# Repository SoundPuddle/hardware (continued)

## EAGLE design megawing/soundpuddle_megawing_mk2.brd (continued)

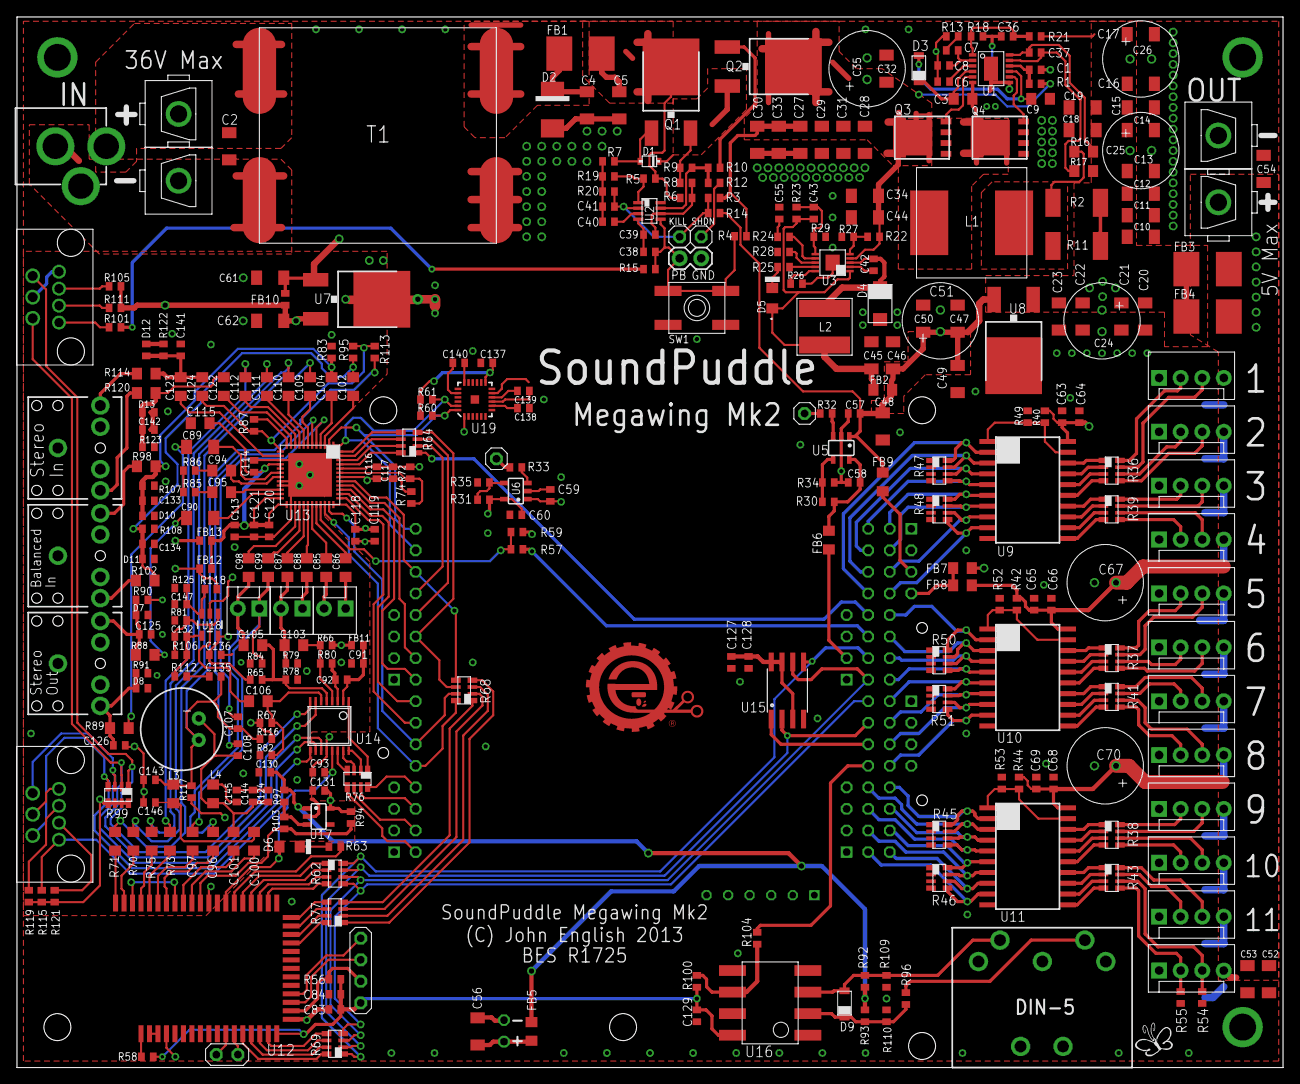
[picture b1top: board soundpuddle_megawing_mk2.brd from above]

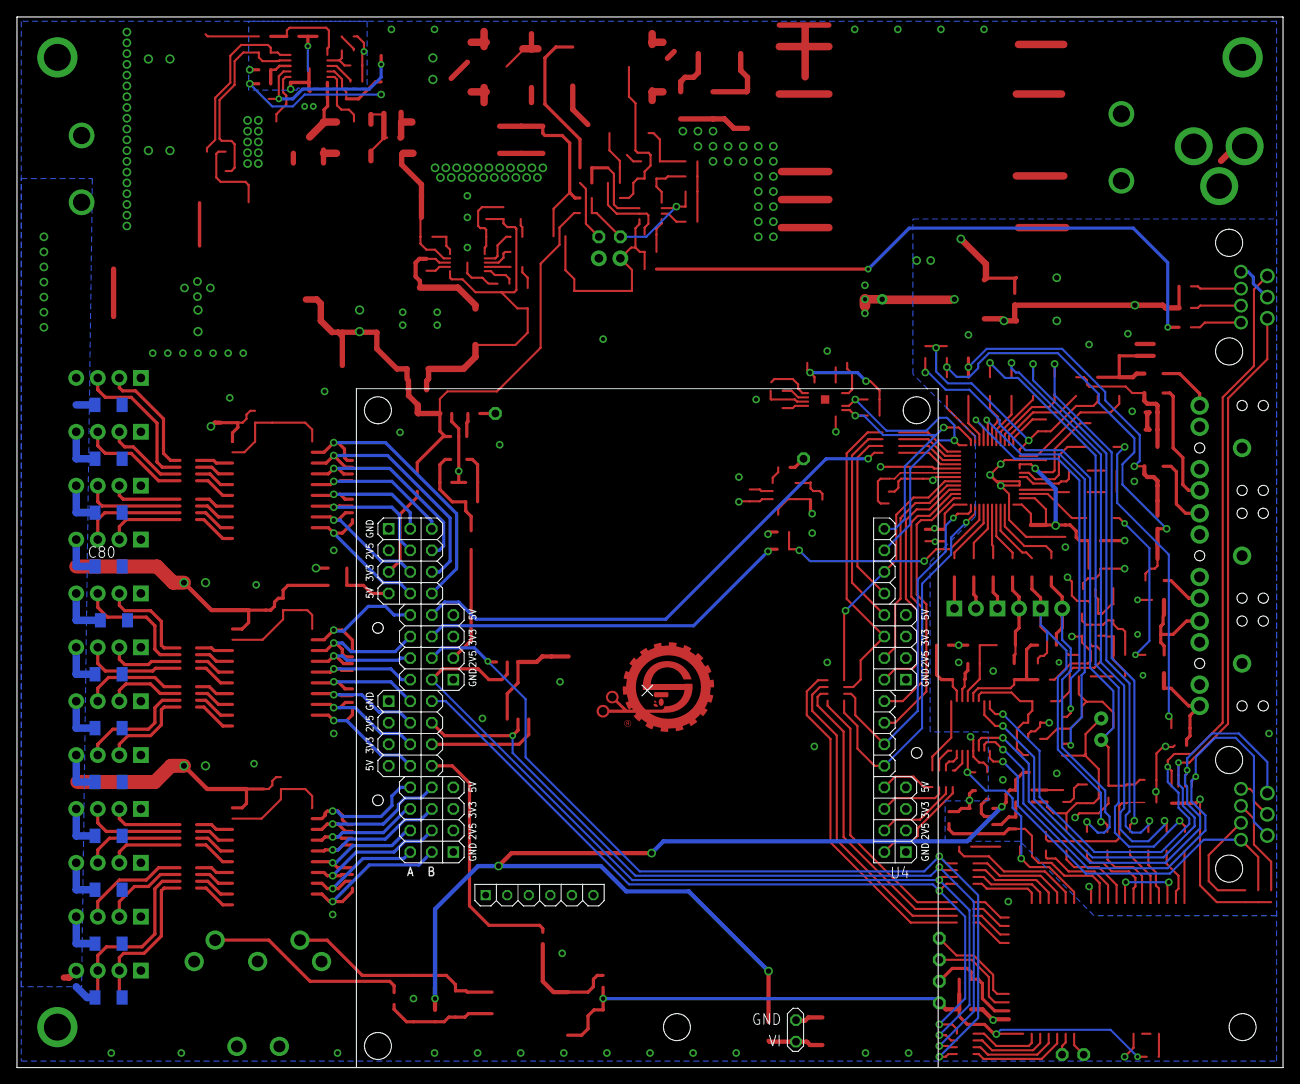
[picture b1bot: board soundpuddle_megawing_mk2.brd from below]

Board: 4 copper layers, 149.2 x 123.8 mm, 363 parts (13 on the bottom side), 279 nets.

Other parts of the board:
U$6: GADGETFACTORY_LOGO

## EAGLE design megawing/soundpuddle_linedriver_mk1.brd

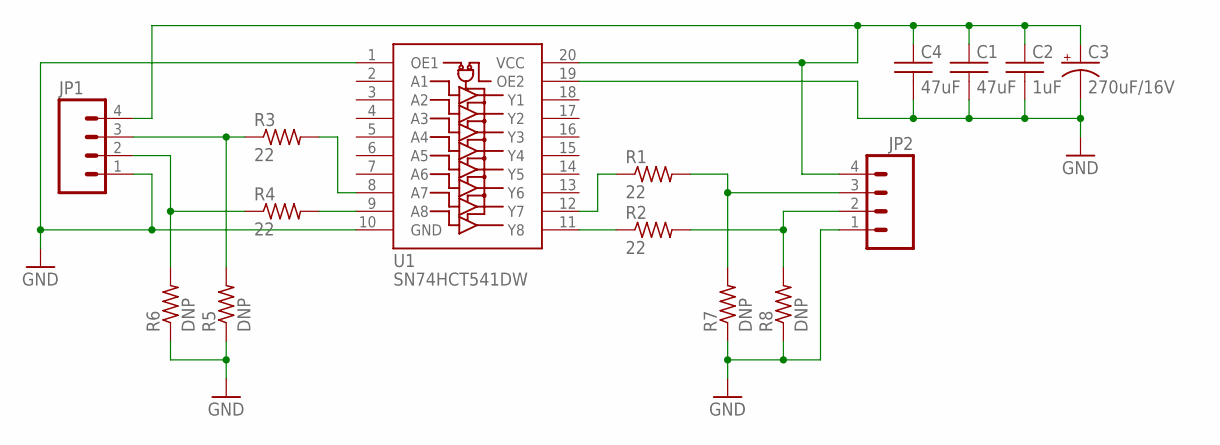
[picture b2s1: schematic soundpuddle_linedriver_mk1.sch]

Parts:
C1, C4: 47uF; 1206
C2: 1uF; 0603
C3: 270uF/16V; CAP_RADIAL_THRUHOLE_8MM_DIA
JP1, JP2: M04POLAR; MOLEX-1X4
R1, R2, R3, R4: 22; 0805
R5, R6, R7, R8: DNP; 0805
U1: SN74HCT541DW; SOIC-20_TI_DW

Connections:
GND: C1.P$2 (2), C2.2, C3.P$1 (-), C4.P$2 (2), JP1.1, JP2.1, R5.1, R6.1, R7.1, R8.1, U1.1 (OE1), U1.10 (GND), U1.19 (OE2)
unnamed: C1.P$1 (1), C2.1, C3.P$2 (+), C4.P$1 (1), JP1.4, JP2.4, U1.20 (VCC)
unnamed: JP1.2, R4.1, R6.2
unnamed: JP1.3, R3.1, R5.2
unnamed: R1.1, U1.12 (Y7)
unnamed: JP2.2, R2.2, R8.2
unnamed: JP2.3, R1.2, R7.2
unnamed: R2.1, U1.11 (Y8)
unnamed: R3.2, U1.8 (A7)
unnamed: R4.2, U1.9 (A8)

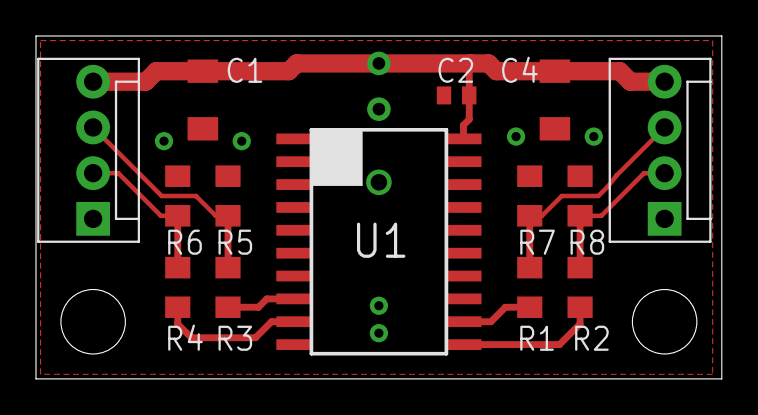
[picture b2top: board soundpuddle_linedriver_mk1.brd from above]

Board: 2 copper layers, 38.1 x 19.1 mm, 15 parts (1 on the bottom side), 10 nets.

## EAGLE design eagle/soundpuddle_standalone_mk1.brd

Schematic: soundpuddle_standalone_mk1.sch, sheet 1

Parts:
$2: changeme; 0603
$3: 3.6uH; INDUCTOR_HC1
C1, C3, C57, C84, C122, C124, C131, C139, C140, C141, C142, C143, C164, C169, C171, C184: 0.1uF; 0603
C2, C4, C14, C15, C18, C21, C26, C31, C43, C44, C53, C54, C58, C61, C104, C106, C107, C108, C109, C113, C127, C134, C136, C138: 1uF; 0603
C5, C6, C8, C9, C10: 10uF; 0805
C7, C17, C23, C25, C34, C45, C46, C47, C48, C56, C69, C70, C71, C72, C73, C74, C75, C76, C79, C80, C112, C115, C118: 1uF; 0805
C11: 22uF; 0603
C12, C13, C20, C130, C133: 22uF; 1206
C16, C126: 0.47uF; 0603
C19, C181, C185, C189, C190: CAPACITOR_ELEC6.3MM_DIA; CAP_RADIAL_THRUHOLE_6.3MM_DIA
C22, C24, C27, C28, C29, C35, C36, C40: 15pF; 0603
C30, C52: 10uF; 0603
C32, C33, C37, C41, C55, C60, C68, C105, C111, C114, C123, C148, C149, C151, C152, C153, C154, C155, C156, C157, C158, C159, C160, C161, C162, C163, C174, C176, C196, C197, C198: 47uF; 1206
C38, C39: 22nF; 0603
C42, C59, C77, C116: 10uF; 1206
C49, C63, C103: 1uF; 1206
C50, C51, C64, C65: 0.22uF; 0603
C62: 220pF; 0603
C66, C82, C110, C119: 33pF; 0603
C67, C117: DNP; 0603
C78, C81, C83, C101: 0.47uF; 0805
C85, C86, C87, C88, C89, C90, C91, C92, C93, C94, C95, C96, C97, C98, C99, C100: .1uF; 0603
C102, C125: 2.2uF; 0603
C120, C121, C165, C168: 22pF; 0603
C128: DNP; 1206
C129: 10pF; 0603
C132: 2.2mF; CAP_RADIAL_THRUHOLE_6.3MM_DIA
C135: 0.1uF; 1206
C137: 1nF; 0603
C144, C145, C146, C147: 1mF; E5-8,5
C150, C172, C173, C175: 47uF; 2220
C166, C183: 2200pF; 0603
C167, C170: 4.7uF; 0603
C177, C178, C191, C192, C193, C194, C195, C199: 100uF; 2220
C179, C180, C186, C187, C188: CAPACITOR_ELEC12.5MM; CAP_RADIAL_THRUHOLE_12.5MM_DIA
C182, C201: 100pF; 0603
C200: 4.7nF; 0603
D1: DNP; DIODE_DO-214AC
D2, D5, D6, D7, D14, D15: LED0603; LED_0603
D3, D13: DIODE_SMDDO-214AC; DIODE_DO-214AC
D4, D16: DIODE_SMDSOD-123F; SOD-123F
D8: DIODE_SMD603; 0603_D
D9: LED0805; LED_0805
D10, D11: RED; LED_0603
D12: DIODE_SMDSOD-323; SOD-323
D17: DIODE_SMDDO-214AB; DIODE_DO-214AB
IC1: LDODPAK; DPACK_1
IC2: MT48LC64M4A2; TSOP54-400
J1: POWER_JACKPTH; POWER_JACK_PTH
J2: AVR_SPI_PRG_6PTH; 2X3
JP1, JP2: M02JST-PTH-2; JST-2-PTH
JP3, JP26, JP28: AUDIO-JACK2PTH; AUDIO-JACK
JP4, JP7, JP11, JP12, JP14, JP18, JP21, JP24, JP27, JP29, JP33, JP34: M04POLAR; MOLEX-1X4
JP5, JP6, JP25, JP35: HEADER-SMALL-1PIN; HEADER-SMALL-1PIN-0.036IN
JP8, JP20, JP22, JP23, JP32: M02PTH; 1X02
JP9: M04PTH; 1X04
JP10, JP31, JP41: HEADER-SMALL-2PIN; HEADER-SMALL-2PIN-0.036IN
JP13, JP17: M02POLAR; MOLEX-1X2
JP15: HEADER-SMALL-3PIN; HEADER-SMALL-3PIN-0.036IN
JP16, JP19, JP36: M05PTH; 1X05
JP30, JP40: USBTHM; USB-MINIB-THM
JP37: HEADER-SMALL-4PIN; HEADER-SMALL-4PIN-0.036IN
JP38: MIDI_CONN_FEMALE_SUPPORT; DIN_5_FEMALE_SUPPORT
JP39: M06SIP; 1X06
L1, L2: INDUCTOR0603; 0603
L3: 6.8uH; INDUCTOR_10X10MM
L4, L5: 15nH; 0805
L6, L7, L8, L9: INDUCTOR0805; 0805
L10, L11, L12, L13: 15uH; 1206
L14: INDUCTOR10X10MM; INDUCTOR_10X10MM
LED1, LED2, LED3: LED0603; LED_0603
MIC1, MIC2: MIC9.7MM; MIC-9.7MM
OSC: 32Mhz; OSC1
Q1: MOSFET-P_CH_DUAL_ARRAYSOIC8; SOIC8
Q2, Q3, Q4, Q5: MOSFET-P_CHANNELDPACK; DPACK_1
Q6, Q7: MOSFET_N_CHANNELLFPAK; POWERPAK_SO-8_LFPAK
R1, R2, R13, R14, R22, R23, R33, R41, R56, R62, R65, R71, R101, R108, R135, R141, R148, R150, R158, R170, R171, R173, R176, R177, R188: DNP; 0603
R3, R8, R15, R28, R32, R63, R75, R82, R98, R100, R117, R119, R145, R151: RESISTOR_ARRAY_4CHCRA06S; RESISTOR_ARRAY_1206_4CH_CRA06S
R4, R5, R6, R7, R9, R10: 10; 0805
R11, R27, R30, R36, R49, R51, R52, R123, R127, R132, R162, R187, R191, R204: 1K; 0603
R12, R34, R37, R38, R39, R40, R53, R58, R59, R60, R66, R74, R104, R114, R116, R137, R143, R146, R159: 100K; 0603
R16, R180, R184, R185, R186, R194, R195: 7.5K; 0603
R17, R44, R61, R64, R80, R85, R91, R118, R120, R139, R142: 2.2K; 0603
R18: 0.033; 1206
R19, R57, R156: 1M; 0603
R20, R21, R24, R26, R45, R67, R76, R78, R79, R93, R94, R106, R131, R133, R144, R149, R157, R161, R165, R167, R168, R169, R172, R193: 10K; 0603
R25, R86, R88: 0; 0603
R29, R35, R77: 121K; 0603
R31: 1K; RESISTOR_ARRAY_1206_4CH_CRA06S
R42, R43, R72, R73, R121, R122: DNP; RESISTOR_ARRAY_1206_4CH_CRA06S
R46, R47, R48, R54, R55: changeme; 0603
R50, R196, R199: 47K; 0603
R68, R99, R147: TRIMPOT3MM-2; TRIMPOT-3MM-2
R69, R89, R92, R95, R96, R102, R107, R111, R113, R115, R125, R163: 1; 0805
R70, R84, R90, R128: 10K; 0805
R81, R83, R110, R124, R129, R140: 43K; 0603
R87: 22; RESISTOR_ARRAY_1206_4CH_CRA06S
R97, R103, R134, R136: 22K; 0603
R105, R138: 39; 0603
R109, R112: 22; 0805
R126, R130, R181, R182: 22; 0603
R152, R153, R164, R178: 330; 0603
R154, R155: 220; 0603
R160: 390; 0603
R166: 562K; 0603
R174, R175, R179: 68; 0603
R183: 1.5K; 0603
R189, R192: 0.006; 2512
R190: 2K; 0603
R197, R198: 16; 1206
R200: 8.06K; 0603
R201: 42.2K; 0603
RT1: 10K; 0603
S8: SWITCH-MOMENTARY-2PTH; TACTILE-PTH
SW3, SW5: SPST_TACT-KMR2; KMR2
U2: ADC128S102; TSSOP16
U3: LTC4002S8; S8_TI
U4, U24, U25: LDO_EN_FB; TSOT23
U5, U11, U14, U17: NJM2068M; DMP8_NJM
U6, U8, U16: SN74HCT541TSSOP20; TSSOP20
U7: LTC2952F; TSSOP20_LT
U9: TPA2008D2; TSSOP24+1_TI
U10: ADXL345; LGA14
U12: WT32; WT32_BT_MODULE
U13: USBLC6-2; SOT23-6L
U15: TPA6130A2QFN20; QFN20+1
U18, U20: TS5A22364DGS; MSOP10
U19: ATMEGA32U4AU; TQFP44
U21, U26: FLASH-SPI-25XXSMD1; SO08-EIAJ
U22: 6N138SMD8; SMD-8
U23: LT3971; MSOP10+1_LT
U27: 6SLX9TQG144; TQ144
U28: FT2232D; LQFP48
U29: 93C46B; SOT23-6
U30: LTC3891; TSSOP20+1_LT
X1: 16Mhz; ABRACOM_CLOCK
X2: ABRACOM_CLOCKS_ABABM10; ABRACOM_CLOCK
~NUDEV~: GND-GNDA

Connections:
1V2: C89.1, C90.1, C91.1, C92.1, U27.19 (VCCINT), U27.28 (VCCINT), U27.52 (VCCINT), U27.89 (VCCINT), U27.128 (VCCINT)
3V3: C85.1, C86.1, C87.1, C88.1, C93.1, C94.1, C95.1, C96.1, C97.1, C98.1, C99.1, C100.1, IC2.1 (VDD), IC2.3 (VDDQ), IC2.9 (VDDQ), IC2.14 (VDD), IC2.27 (VDD), IC2.43 (VDDQ), IC2.49 (VDDQ), OSC.1@1 (OE), OSC.4@4 (VCC), R199.2, U26.3 (WP), U26.7 (HOLD), U26.8 (VCC), U27.4 (VCCO_3), U27.18 (VCCO_3), U27.20 (VCCAUX), U27.31 (VCCO_3), U27.36 (VCCAUX), U27.42 (VCCO_2), U27.53 (VCCAUX), U27.63 (VCCO_2), U27.69 (IO_L1N_M0_CMPMISO_2), U27.76 (VCCO_1), U27.86 (VCCO_1), U27.90 (VCCAUX), U27.103 (VCCO_1), U27.122 (VCCO_0), U27.125 (VCCO_0), U27.129 (VCCAUX), U27.135 (VCCO_0)
3V3OUT_A: C142.2, U28.6 (3V3OUT)
!CAS: IC2.17 (!CAS), U27.5 (IO_L52N_3)
!RAS: IC2.18 (!RAS), U27.2 (IO_L83P_3)
!WE: IC2.16 (!WE), U27.6 (IO_L52P_3)
+3V3: C54.1, C57.1, C58.1, C59.P$1 (1), C106.1, C107.1, C108.1, C127.1, C128.P$1 (1), C129.1, C132.P$2 (+), C133.P$1 (1), C134.1, C135.P$1 (1), C138.1, D9.1 (A), D14.1 (A), J2.2, JP16.5, JP39.6, L2.1, L14.P$2 (2), LED1.1 (A), LED2.1 (A), R74.2, R75.P$4 (1), R131.2, R155.2, R156.2, R171.2, U10.1 (VDD), U10.6 (VSS), U10.7 (CS), U12.17 (VDDIO), U12.37 (VDD_BAT), U19.14 (VCC), U19.24 (AVCC), U19.34 (VCC), U19.44 (AVCC), U21.3 (WP), U21.7 (HOLD), U21.8 (VCC), U22.P$8 (VCC), U23.P$1 (BD), U24.1 (IN), U25.5 (OUT), U28.10 (SI/WUA), U28.14 (VCCIOA), U28.26 (SI/WUB), U28.31 (VCCIOB)
+5V: C18.1, C30.1, C31.1, C32.P$2 (2), C33.P$2 (2), C37.P$2 (2), C41.P$2 (2), C42.P$1 (1), C43.1, C44.1, C52.1, C53.1, C55.P$2 (2), C60.P$2 (2), C68.P$2 (2), C103.P$1 (1), C104.1, C105.P$2 (2), C111.P$2 (2), C114.P$2 (2), C123.P$2 (2), C139.1, C140.1, C144.+, C145.+, C146.+, C147.+, C148.P$1 (1), C149.P$1 (1), C150.P$1 (1), C151.P$1 (1), C152.P$1 (1), C153.P$1 (1), C154.P$1 (1), C155.P$1 (1), C156.P$1 (1), C157.P$1 (1), C158.P$1 (1), C159.P$1 (1), C160.P$1 (1), C161.P$1 (1), C162.P$1 (1), C163.P$1 (1), C164.1, C169.1, C185.P$2 (+), C186.P$2 (+), C187.P$2 (+), C188.P$2 (+), C189.P$2 (+), C190.P$2 (+), C191.P$1 (1), C192.P$1 (1), C193.P$1 (1), C194.P$1 (1), C195.P$1 (1), C196.P$1 (1), C197.P$1 (1), C198.P$1 (1), C199.P$1 (1), IC1.3 (2_VIN), JP4.4, JP7.4, JP11.4, JP12.4, JP14.4, JP18.4, JP21.4, JP24.4, JP27.4, JP29.4, JP33.4, JP34.4, R23.2, R31.P$6 (2), R31.P$7 (2), R31.P$8 (2), R33.2, R62.1, R65.1, R135.2, R152.2, R153.2, R180.1, R189.1, R191.2, R192.1, R193.1, R198.P$1 (1), R200.2, U4.1 (IN), U6.20 (VCC), U8.20 (VCC), U9.4 (PVDDL), U9.9 (PVDDL), U9.13 (VDD), U9.16 (PVDDR), U9.21 (PVDDR), U16.20 (VCC), U25.1 (IN), U28.3 (VCC), U28.4 (RESET#), U28.42 (VCC), U29.6 (VCC)
A0: IC2.23 (A0), U27.140 (IO_L3P_0)
A1: IC2.24 (A1), U27.139 (IO_L3N_0)
A2: IC2.25 (A2), U27.138 (IO_L4P_0)
A3: IC2.26 (A3), U27.137 (IO_L4N_0)
A4: IC2.29 (A4), U27.46 (IO_L49P_D3_2)
A5: IC2.30 (A5), U27.45 (IO_L49N_D4_2)
A6: IC2.31 (A6), U27.44 (IO_L62P_D5_2)
A7: IC2.32 (A7), U27.43 (IO_L62N_D6_2)
A8: IC2.33 (A8), U27.41 (IO_L64P_D8_2)
A9: IC2.34 (A9), U27.40 (IO_L64N_D9_2)
A10: IC2.22 (A10), U27.141 (IO_L2N_0)
A11: IC2.35 (A11), U27.35 (IO_L1P_3)
A12: IC2.36 (A12), U27.34 (IO_L1N_VREF_3)
ACC_INT1: JP15.P$1, U10.8 (INT1)
ACC_INT2: JP15.P$2, U10.9 (INT2)
ADC_CS: R8.P$8 (2)
ADC_IN2: C5.2, R1.1, R13.2
ADC_IN3: C6.2, R2.1, R14.2
ADC_IN4: C7.2, R3.P$1 (1), R15.P$8 (2), U2.7 (IN3)
ADC_IN5: C8.2, R3.P$2 (1), R15.P$7 (2), U2.6 (IN2)
ADC_IN6: C9.2, R3.P$3 (1), R15.P$6 (2), U2.5 (IN1)
ADC_IN7: C10.2, R3.P$4 (1), R15.P$5 (2), U2.4 (IN0)
ADC_MISO: R8.P$6 (2)
ADC_MOSI: R8.P$7 (2)
ADC_SCK: R8.P$5 (2)
AOL_N: R89.2, U18.4 (NC1)
AOL_P: R92.2, U18.8 (NC2)
AOR_N: R95.2, U20.4 (NC1)
AOR_P: R96.2, U20.8 (NC2)
AREF: C124.1, R135.1, R141.2, U19.42 (AREF)
ATMEGA_MISO: U19.11 (PB3(MISO))
ATMEGA_MOSI: U19.10 (PB2(MOSI))
ATMEGA_SCK: U19.9 (PB1(SCK))
AUX_IN_L: C56.1, JP26.TIP, R9.1
AUX_IN_L_N: R115.2, U18.2 (N01)
AUX_IN_L_P: R69.2, U18.10 (N02)
AUX_IN_R: C112.1, JP26.RING, R10.1
AUX_IN_R_N: R163.2, U20.2 (N01)
AUX_IN_R_P: R125.2, U20.10 (N02)
AUX_OUT_L: C116.P$2 (2), JP28.TIP, R6.1, R109.2, R137.2, R138.2
AUX_OUT_R: C77.P$2 (2), JP28.RING, R7.1, R104.2, R105.2, R112.2
BA0: IC2.20 (BA0), U27.143 (IO_L1N_VREF_0)
BA1: IC2.21 (BA1), U27.142 (IO_L2P_0)
BT_CLK: JP19.4, U12.33 (SPI_CLK)
BT_CTS: JP16.1, R75.P$8 (2)
BT_MIC_BIAS: R20.2, U12.40 (MIC_BIAS)
BT_MISO: JP19.3, U12.34 (SPI_MISO)
BT_MOSI: JP19.2, U12.35 (SPI_MOSI)
BT_PIO2: R98.P$4 (1)
BT_PIO3: R98.P$3 (1)
BT_PIO9: R87.P$1 (1)
BT_PIO10: R87.P$2 (1)
BT_RTS: JP16.2, R75.P$7 (2)
BT_RXD: R87.P$3 (1)
BT_SPICS: JP19.5, U12.32 (SPI_CS)
BT_TXD: R87.P$4 (1)
BUFFER_EN: R33.1, R44.2, U6.1 (OE1), U6.19 (OE2), U8.1 (OE1), U8.19 (OE2), U16.1 (OE1), U16.19 (OE2)
C4: R160.2
CKE: IC2.37 (CKE), U27.33 (IO_L2P_3)
CLK: IC2.38 (CLK), U27.32 (IO_L2N_3)
CS: IC2.19 (\CS), U27.1 (IO_L83N_VREF_3)
D+: JP30.D+, R130.2, R177.2, U13.1 (IO1A)
D+1: JP40.D+, R177.1, R182.1
D+_IC: R126.1, U19.3 (D-)
D-: JP30.D-, R126.2, R176.2, U13.3 (IO2A)
D-1: JP40.D-, R176.1, R181.1
D-_IC: R130.1, U19.4 (D+)
DO_A: R190.1, R193.2, U29.1 (DO)
DQ0: IC2.2 (DQ0), U27.9 (IO_L50N_3)
DQ1: IC2.4 (DQ1), U27.10 (IO_L50P_3)
DQ2: IC2.5 (DQ2), U27.11 (IO_L49N_3)
DQ3: IC2.7 (DQ3), U27.12 (IO_L49P_3)
DQ4: IC2.8 (DQ4), U27.14 (IO_L44N_GCLK20_3)
DQ5: IC2.10 (DQ5), U27.15 (IO_L44P_GCLK21_3)
DQ6: IC2.11 (DQ6), U27.16 (IO_L43N_GCLK22_IRDY2_3)
DQ7: IC2.13 (DQ7), U27.8 (IO_L51P_3)
DQ8: IC2.42 (DQ8), U27.21 (IO_L42N_GCLK24_3)
DQ9: IC2.44 (DQ9), U27.22 (IO_L42P_GCLK25_TRDY2_3)
DQ10: IC2.45 (DQ10), U27.23 (IO_L41N_GCLK26_3)
DQ11: IC2.47 (DQ11), U27.24 (IO_L41P_GCLK27_3)
DQ12: IC2.48 (DQ12), U27.26 (IO_L37N_3)
DQ13: IC2.50 (DQ13), U27.27 (IO_L37P_3)
DQ14: IC2.51 (DQ14), U27.29 (IO_L36N_3)
DQ15: IC2.53 (DQ15), U27.30 (IO_L36P_3)
DQMH: IC2.39 (DQMH), U27.17 (IO_L43P_GCLK23_3)
DQML: IC2.15 (DQML), U27.7 (IO_L51N_3)
EECS_A: U28.48 (EECS), U29.5 (CS)
EEDATA_A: R190.2, U28.2 (EEDATA), U29.3 (DI)
EESK: U28.1 (EESK), U29.4 (CLK)
EN: R45.1, U7.P$14 (EN)
FILTERED_VCC_A: C141.2, R191.1, U28.46 (AVCC)
FLASH_CS: U21.1 (CS), U26.1 (CS), U27.38 (IO_L65N_CSO_B_2)
FLASH_MISO: U21.2 (MISO)
FLASH_MOSI: U21.5 (MOSI)
FLASH_SCK: U21.6 (SCK), U26.6 (SCK), U27.70 (IO_L1P_CCLK_2)
FLASH_SI: U26.5 (MOSI), U27.64 (IO_L3N_MOSI_CSI_B_MISO0_2)
FLASH_SO: U26.2 (MISO), U27.65 (IO_L3P_D0_DIN_MISO_MISO1_2)
GND: $2.1, C1.2, C2.2, C3.2, C4.2, C11.2, C12.P$2 (2), C13.P$2 (2), C14.2, C15.2, C19.P$1 (-), C20.P$2 (2), C21.2, C30.2, C31.2, C32.P$1 (1), C33.P$1 (1), C37.P$1 (1), C38.2, C39.2, C41.P$1 (1), C52.2, C53.2, C54.2, C55.P$1 (1), C57.2, C58.2, C59.P$2 (2), C60.P$1 (1), C68.P$1 (1), C85.2, C86.2, C87.2, C88.2, C89.2, C90.2, C91.2, C92.2, C93.2, C94.2, C95.2, C96.2, C97.2, C98.2, C99.2, C100.2, C103.P$2 (2), C104.2, C105.P$1 (1), C106.2, C107.2, C108.2, C109.2, C111.P$1 (1), C113.2, C114.P$1 (1), C120.2, C121.2, C123.P$1 (1), C124.2, C127.2, C128.P$2 (2), C130.P$2 (2), C131.2, C132.P$1 (-), C133.P$2 (2), C134.2, C135.P$2 (2), C136.2, C137.2, C138.2, C139.2, C140.2, C141.1, C142.1, C143.2, C144.-, C145.-, C146.-, C147.-, C148.P$2 (2), C149.P$2 (2), C150.P$2 (2), C151.P$2 (2), C152.P$2 (2), C153.P$2 (2), C154.P$2 (2), C155.P$2 (2), C156.P$2 (2), C157.P$2 (2), C158.P$2 (2), C159.P$2 (2), C160.P$2 (2), C161.P$2 (2), C162.P$2 (2), C163.P$2 (2), C164.2, C165.1, C166.2, C167.2, C168.1, C169.2, C172.P$2 (2), C173.P$2 (2), C174.P$2 (2), C175.P$2 (2), C176.P$2 (2), C177.P$2 (2), C178.P$2 (2), C179.P$1 (-), C180.P$1 (-), C181.P$1 (-), C185.P$1 (-), C186.P$1 (-), C187.P$1 (-), C188.P$1 (-), C189.P$1 (-), C190.P$1 (-), C191.P$2 (2), C192.P$2 (2), C193.P$2 (2), C194.P$2 (2), C195.P$2 (2), C196.P$2 (2), C197.P$2 (2), C198.P$2 (2), C199.P$2 (2), D3.P$2 (A), D13.P$2 (A), D17.A, IC1.1 (1_GND), IC2.6 (VSSQ), IC2.12 (VSSQ), IC2.28 (VSS), IC2.41 (VSS), IC2.46 (VSSQ), IC2.52 (VSSQ), IC2.54 (VSS), J1.GND, J1.GNDBREAK, J2.6, JP1.1, JP2.1, JP4.1, JP7.1, JP9.1, JP11.1, JP12.1, JP14.1, JP15.P$3, JP18.1, JP19.1, JP21.1, JP24.1, JP27.1, JP29.1, JP30.GND, JP33.1, JP34.1, JP36.1, JP37.P$4, JP39.5, JP40.GND, JP41.P$1, LED3.2 (C), OSC.2@2 (GND), Q7.1S (S), Q7.2S (S), Q7.3S (S), R13.1, R14.1, R15.P$1 (1), R15.P$2 (1), R15.P$3 (1), R15.P$4 (1), R17.2, R35.1, R42.P$1 (1), R42.P$2 (1), R42.P$3 (1), R42.P$4 (1), R43.P$1 (1), R43.P$2 (1), R43.P$3 (1), R43.P$4 (1), R44.1, R54.1, R55.1, R72.P$1 (1), R72.P$2 (1), R72.P$3 (1), R72.P$4 (1), R73.P$1 (1), R73.P$2 (1), R73.P$3 (1), R73.P$4 (1), R90.2, R121.P$1 (1), R121.P$2 (1), R121.P$3 (1), R121.P$4 (1), R122.P$1 (1), R122.P$2 (1), R122.P$3 (1), R122.P$4 (1), R123.2, R127.2, R132.2, R141.1, R164.1, R165.1, R166.1, R168.1, R169.1, R170.1, R173.1, R178.1, RT1.2, S8.1, SW3.2 (S), SW3.4 (S1), SW5.2 (S), SW5.4 (S1), U2.3 (AGND), U2.12 (DGND), U3.P$4 (GND), U6.10 (GND), U7.P$12 (GND), U8.10 (GND), U9.6 (PGNDL), U9.7 (PGNDL), U9.18 (PGNDR), U9.19 (PGNDR), U10.2 (GND), U10.4 (GND), U10.5 (GND), U10.12 (SDO), U12.2 (DGND), U12.3 (DGND), U12.4 (DGND), U12.18 (DGND), U12.31 (DGND), U13.2 (GND), U16.10 (GND), U19.5 (UGND), U19.15 (GND), U19.23 (GND), U19.35 (GND), U19.43 (GND), U21.4 (GND), U22.P$5 (GND), U23.P$11 (GND), U24.2 (GND), U25.2 (GND), U26.4 (GND), U27.3 (GND), U27.13 (GND), U27.25 (GND), U27.49 (GND), U27.54 (GND), U27.60 (IO_L13P_M1_2), U27.68 (GND), U27.73 (SUSPEND), U27.77 (GND), U27.91 (GND), U27.96 (GND), U27.108 (GND), U27.113 (GND), U27.130 (GND), U27.136 (GND), U27.144 (IO_L1P_HSWAPEN_0), U28.9 (GND), U28.18 (GND), U28.25 (GND), U28.34 (GND), U28.45 (GND), U28.47 (TEST), U29.2 (GND), U30.P$11 (PGND), X1.2, X1.4, X2.2, X2.4
GNDA: C17.2, C18.2, C24.1, C26.2, C27.2, C28.2, C29.2, C40.2, C42.P$2 (2), C43.2, C44.2, C50.2, C51.2, C61.2, C62.2, C64.2, C65.2, C73.2, C74.2, C75.2, C84.2, C102.2, C122.2, C125.2, JP3.SLEEVE, JP8.1, JP20.1, JP26.SLEEVE, JP28.SLEEVE, JP31.P$1, MIC2.1, R26.1, R27.1, R58.1, R59.1, R68.3 (CW), R71.1, R76.1, R77.1, R104.1, R106.1, R116.1, R137.1, R146.1, R149.1, U4.2 (GND), U5.4 (V-), U9.12 (AGND), U9.PGND (AGND), U11.4 (V-), U12.39 (AGND), U12.43 (AGND), U12.48 (AGND), U14.4 (V-), U15.P$3 (GND), U15.P$9 (GND), U15.P$10 (GND), U15.P$13 (GND), U15.P$19 (GND), U15.PAD (GND), U17.4 (V-), U18.6 (GND), U20.6 (GND)
GNDIO: C171.2, C182.2, C183.2, C184.2, C201.2, R188.1, R195.1, R201.1, U30.P$4 (SGND), U30.P$5 (SGND), U30.PAD (SGND)
LED1: R196.2, U27.112 (IO_L66P_SCP1_0)
LED_B1: U19.30 (PB6(D10*/A11))
LED_G1: U19.31 (PC6(D5*))
LED_R1: U19.32 (PC7(D13*))
LOUT_N: C45.1, C78.1, C80.1, U18.3 (COM1)
LOUT_P: C46.1, C76.1, C81.1, U18.9 (COM2)
MIC_DYNAMIC: R4.1, R66.2, U5.7 (OUT)
MIC_ELECTRET: C22.2, R5.1, R19.2, U5.1 (OUT)
MIC_N: C25.1, C28.1, C69.2, L5.1
MIC_P: C23.1, C29.1, C70.2, L4.1
MIC_REG: C17.1, R30.2, R84.2, U4.5 (OUT)
MISO: J2.1
MOSI: J2.4
MUX_IN1: JP31.P$2, R145.P$5 (2), R145.P$6 (2), R145.P$7 (2), R145.P$8 (2), U19.12 (PB7(D11*))
unnamed: C120.1, U19.16 (XTAL2), X1.3 (3A)
unnamed: C35.1, R50.2, R52.2, U5.5 (+)
unnamed: C5.1, R4.2
unnamed: C36.1, R40.1, R50.1, R53.1, R59.2
unnamed: R94.2, U15.P$6 (SD)
unnamed: D11.2 (C), R132.1
unnamed: C112.2, R128.1
unnamed: R20.1, R23.1, U4.3 (EN)
unnamed: C56.2, R70.1
unnamed: R96.1, U12.47 (AUDIO_OUT_P_RIGHT)
unnamed: C121.1, U19.17 (XTAL1), X1.1 (1A)
unnamed: C26.1, R21.1, R25.2, R26.2, U5.3 (+)
unnamed: R123.1, U19.33 (PE2(HWB))
unnamed: L3.P$2 (2), R18.P$2 (2), U3.P$7 (SENSE)
unnamed: R183.2, U28.5 (RSTOUT#)
unnamed: R36.2, U7.P$19 (G1)
unnamed: C45.2, L6.1
unnamed: C113.1, U19.6 (UCAP)
unnamed: D2.1 (A), R11.1
unnamed: C46.2, L7.1
unnamed: C47.2, L8.1
unnamed: C48.2, L9.1
unnamed: R77.2, U9.11 (ROSC)
unnamed: C62.1, U9.10 (COSC)
unnamed: C7.1, R6.2
unnamed: C49.P$1 (1), C50.1, JP13.1, L10.P$2 (2)
unnamed: Q4.1 (G), Q5.1 (G), R36.1
unnamed: L10.P$1 (1), U9.8 (LOUTN)
unnamed: C61.1, U9.22 (BYPASS)
unnamed: L11.P$1 (1), U9.5 (LOUTP)
unnamed: C49.P$2 (2), C51.1, JP13.2, L11.P$2 (2)
unnamed: L13.P$1 (1), U9.20 (ROUTP)
unnamed: L12.P$1 (1), U9.17 (ROUTN)
unnamed: C63.P$1 (1), C64.1, JP17.2, L12.P$2 (2)
unnamed: C63.P$2 (2), C65.1, JP17.1, L13.P$2 (2)
unnamed: JP36.3, R151.P$6 (2)
unnamed: JP36.2, R151.P$5 (2)
unnamed: Q2.1 (G), Q3.1 (G), U7.P$15 (G2)
unnamed: R29.1, R35.2, R41.1, U7.P$5 (PFI)
unnamed: L9.2, U9.23 (RINP)
unnamed: L8.2, U9.24 (RINN)
unnamed: L7.2, U9.2 (LINP)
unnamed: L6.2, U9.1 (LINN)
unnamed: C27.1, JP3.RING, L5.2, MIC1.1, R27.2
unnamed: C24.2, JP3.TIP, L4.2, MIC1.2, R22.1, R30.1
unnamed: C69.1, U12.44 (AUDIO_IN_P_LEFT)
unnamed: C70.1, U12.45 (AUDIO_IN_N_LEFT)
unnamed: S8.3 (2), U7.P$7 (_PB)
unnamed: R48.1, R55.2, U7.P$1 (M2)
unnamed: $2.2, R47.1, U7.P$2 (M1)
unnamed: R80.1, U12.36 (LED0)
unnamed: Q1.4 (G), U3.P$3 (GATE)
unnamed: C13.P$1 (1), C14.1, C15.1, D1.P$1 (C), Q1.1 (S), Q1.3 (S), U3.P$2 (VCC)
unnamed: R98.P$5 (2), U12.9 (PIO2)
unnamed: C23.2, R24.1
unnamed: C16.1, U3.P$1 (COMP)
unnamed: C16.2, R17.1
unnamed: RT1.1, U3.P$8 (NTC)
unnamed: D3.P$1 (C), L3.P$1 (1), Q1.5 (D), Q1.6 (D)
unnamed: R98.P$6 (2), U12.10 (PIO3)
unnamed: R87.P$8 (2), U12.13 (PIO9)
unnamed: R87.P$7 (2), U12.14 (PIO10)
unnamed: R95.1, U12.46 (AUDIO_OUT_N_RIGHT)
unnamed: D9.2 (C), R80.2
unnamed: C67.2, R61.2, R78.2, R91.2, R108.2, R115.1, U11.7 (OUT)
unnamed: R92.1, U12.50 (AUDIO_OUT_P_LEFT)
unnamed: R98.P$1 (1), U13.4 (IO2B)
unnamed: JP16.4, R75.P$5 (2)
unnamed: C39.1, U7.P$11 (OFFT)
unnamed: JP16.3, R75.P$6 (2)
unnamed: R98.P$8 (2), U12.12 (USB_DP)
unnamed: R98.P$7 (2), U12.11 (USB_DN)
unnamed: C25.2, R25.1
unnamed: JP36.5, R151.P$8 (2)
unnamed: C38.1, U7.P$10 (ONT)
unnamed: D5.1 (A), R31.P$2 (1)
unnamed: D7.1 (A), R31.P$3 (1)
unnamed: Q2.3 (S), Q3.3 (S)
unnamed: D6.1 (A), R31.P$1 (1)
unnamed: D5.2 (C), U7.P$8 (_RST)
unnamed: LED3.1 (A), R196.1
unnamed: C126.2, D13.P$1 (C), L14.P$1 (1), U23.P$3 (SW)
unnamed: D6.2 (C), U7.P$20 (G1STAT)
unnamed: R87.P$6 (2), U12.15 (RXD)
unnamed: R87.P$5 (2), U12.16 (TXD)
unnamed: D7.2 (C), U7.P$9 (_PFO)
unnamed: C22.1, R19.1, R24.2, U5.2 (-)
unnamed: JP9.4, U7.P$13 (_INT)
unnamed: R49.2, U7.P$18 (V1)
unnamed: R51.2, U7.P$16 (V2)
unnamed: C126.1, U23.P$2 (BOOST)
unnamed: R98.P$2 (1), U13.6 (IO1B)
unnamed: C101.2, R113.1
unnamed: C83.2, R111.1
unnamed: C81.2, R107.1
unnamed: C78.2, R102.1
unnamed: R102.2, U15.P$1 (LEFTINM)
unnamed: R107.2, U15.P$2 (LEFTINP)
unnamed: R75.P$1 (1), U12.21 (CTS)
unnamed: R75.P$2 (1), U12.20 (RTS)
unnamed: R111.2, U15.P$5 (RIGHTINM)
unnamed: R113.2, U15.P$4 (RIGHTIMP)
unnamed: R74.1, R79.2, U12.1 (VREG_ENA)
unnamed: C35.2, C36.2
unnamed: C73.1, U15.P$15 (CPVSS), U15.P$16 (CPVSS)
unnamed: R109.1, U15.P$14 (HPLEFT)
unnamed: C79.1, U15.P$18 (CPP)
unnamed: C79.2, U15.P$17 (CPN)
unnamed: D8.ANNODE(1) (A), R79.1
unnamed: R112.1, U15.P$11 (HPRIGHT)
unnamed: C34.2, R52.1
unnamed: C6.1, R5.2
unnamed: R172.2, U25.3 (EN)
unnamed: C34.1, JP8.2, MIC2.2, R37.1, R38.1, R39.1, R58.2
unnamed: R57.1, U5.6 (-)
unnamed: R89.1, U12.49 (AUDIO_OUT_N_LEFT)
unnamed: C117.2, R118.2, R133.2, R142.2, R150.2, R163.1, U17.7 (OUT)
unnamed: R120.2, R125.1, R139.2, U17.1 (OUT)
unnamed: C40.1, R60.1
unnamed: R57.2, R60.2, R66.1
unnamed: JP6.P$1, R40.2
unnamed: R75.P$3 (1), U12.19 (RESET)
unnamed: LED1.2 (C), R187.2
unnamed: R171.1, R173.2, U25.4 (FB)
unnamed: D14.2 (C), R162.2
unnamed: Q4.3 (S), Q5.3 (S)
unnamed: R162.1, U23.P$9 (PG)
unnamed: D2.2 (C), Q1.2 (G), R12.1, U3.P$5 (CHRG)
unnamed: R100.P$8 (2), U12.27 (PCM_IN)
unnamed: R158.1, R170.2, U24.4 (FB)
unnamed: C129.2, R156.1, R166.2, U23.P$6 (FB)
unnamed: R100.P$7 (2), U12.28 (PCM_OUT)
unnamed: C66.1, JP22.2, R81.1, R97.2, R99.2 (WIPER), U14.2 (-)
unnamed: C82.1, R103.2, R110.2, U14.3 (+)
unnamed: C76.2, R97.1
unnamed: C80.2, R103.1
unnamed: C71.1, U12.41 (AUDIO_IN_P_RIGHT)
unnamed: C72.1, U12.42 (AUDIO_IN_N_RIGHT)
unnamed: C66.2, C77.P$1 (1), R81.2, R83.2, U14.1 (OUT)
unnamed: C82.2, C102.1, R110.1, R114.1, R116.2
unnamed: C84.1, R105.1
unnamed: R167.2, U24.3 (EN)
unnamed: R165.2, U23.P$10 (SYNC)
unnamed: JP32.2, R129.1, R147.2 (WIPER)
unnamed: C119.1, R136.2, R140.2, U14.5 (+)
unnamed: C115.2, R134.1
unnamed: C118.2, R136.1
unnamed: C137.1, R159.1
unnamed: R139.1, R142.1, U17.6 (-)
unnamed: C110.2, C116.P$1 (1), R124.2, R129.2, U14.7 (OUT)
unnamed: C119.2, C125.1, R140.1, R143.1, R146.2
unnamed: R169.2, U23.P$8 (RT)
unnamed: C122.1, R138.1
unnamed: JP5.P$1, R38.2
unnamed: R100.P$6 (2), U12.29 (PCM_SYNC)
unnamed: R159.2, U23.P$7 (SS)
unnamed: R145.P$4 (1), U18.5 (IN1)
unnamed: R145.P$3 (1), U18.7 (IN2)
unnamed: R100.P$5 (2), U12.30 (PCM_CLK)
unnamed: R157.1, R161.2, R168.2, U23.P$5 (EN)
unnamed: LED2.2 (C), R204.2
unnamed: JP37.P$2, JP38.5 (MIDI_OUT), R154.1
unnamed: JP36.4, R151.P$7 (2)
unnamed: R145.P$2 (1), U20.5 (IN1)
unnamed: R145.P$1 (1), U20.7 (IN2)
unnamed: D12.C, R153.1, R154.2, R164.2, U22.P$2 (A)
unnamed: R118.1, R120.1, U17.2 (-)
unnamed: R85.1, R91.1, U11.6 (-)
unnamed: C117.1, R128.2, R133.1, U17.3 (+)
unnamed: JP35.P$1, R148.1
unnamed: C8.1, R7.2
unnamed: R144.1, R148.2, R149.2, R150.1, U17.5 (+)
unnamed: D12.A, JP37.P$1, JP38.4 (MIDI_IN), R152.1, R178.2, U22.P$3 (C)
unnamed: JP22.1, R83.1, R99.3 (CW)
unnamed: R61.1, R64.1, U11.2 (-)
unnamed: C67.1, R70.2, R78.1, U11.3 (+)
unnamed: R155.1, R160.1, U22.P$6 (VO)
unnamed: C72.2, JP23.1, R90.1
unnamed: R93.1, R101.2, R106.2, R108.1, U11.5 (+)
unnamed: JP25.P$1, R101.1
unnamed: C71.2, JP23.2, R84.1
unnamed: C110.1, JP32.1, R124.1, R134.2, R147.3 (CW), U14.6 (-)
unnamed: R32.P$1 (1), U6.14 (Y5)
unnamed: R28.P$1 (1), U6.18 (Y1)
unnamed: R28.P$2 (1), U6.17 (Y2)
unnamed: R28.P$3 (1), U6.16 (Y3)
unnamed: R28.P$4 (1), U6.15 (Y4)
unnamed: R32.P$2 (1), U6.13 (Y6)
unnamed: R32.P$3 (1), U6.12 (Y7)
unnamed: R32.P$4 (1), U6.11 (Y8)
unnamed: JP11.2, R32.P$8 (2)
unnamed: JP11.3, R32.P$7 (2)
unnamed: JP7.3, R28.P$5 (2)
unnamed: JP7.2, R28.P$6 (2)
unnamed: JP4.3, R28.P$7 (2)
unnamed: JP4.2, R28.P$8 (2)
unnamed: C3.1, C4.1, L2.2, U2.13 (VD)
unnamed: C1.1, C2.1, L1.2, U2.2 (VA)
unnamed: D10.2 (C), R127.1
unnamed: R82.P$1 (1), U8.14 (Y5)
unnamed: R63.P$1 (1), U8.18 (Y1)
unnamed: R63.P$2 (1), U8.17 (Y2)
unnamed: R63.P$3 (1), U8.16 (Y3)
unnamed: R63.P$4 (1), U8.15 (Y4)
unnamed: R82.P$2 (1), U8.13 (Y6)
unnamed: R82.P$3 (1), U8.12 (Y7)
unnamed: R82.P$4 (1), U8.11 (Y8)
unnamed: JP21.2, R82.P$8 (2)
unnamed: JP21.3, R82.P$7 (2)
unnamed: JP18.3, R63.P$5 (2)
unnamed: JP18.2, R63.P$6 (2)
unnamed: JP14.3, R63.P$7 (2)
unnamed: JP14.2, R63.P$8 (2)
unnamed: R64.2, R69.1, R85.2, U11.1 (OUT)
unnamed: R119.P$1 (1), U16.14 (Y5)
unnamed: R117.P$1 (1), U16.18 (Y1)
unnamed: $3.P$1 (1), C170.2, D17.C, Q6.1S (S), Q6.2S (S), Q6.3S (S), Q7.PAD (D), Q7.PAD2 (D), U30.P$13 (SW)
unnamed: R117.P$2 (1), U16.17 (Y2)
unnamed: R117.P$3 (1), U16.16 (Y3)
unnamed: C182.1, R194.2, U30.P$10 (ITH)
unnamed: C200.1, R197.P$2 (2), U30.P$8 (SENSE+)
unnamed: C200.2, R198.P$2 (2), U30.P$7 (SENSE-)
unnamed: $3.P$2 (2), R189.2, R192.2, R197.P$1 (1)
unnamed: C167.1, D16.P$2 (A), R16.2, U30.P$16 (INTVCC)
unnamed: R117.P$4 (1), U16.15 (Y4)
unnamed: R119.P$2 (1), U16.13 (Y6)
unnamed: R119.P$3 (1), U16.12 (Y7)
unnamed: R119.P$4 (1), U16.11 (Y8)
unnamed: JP33.2, R119.P$8 (2)
unnamed: JP33.3, R119.P$7 (2)
unnamed: JP29.3, R117.P$5 (2)
unnamed: JP29.2, R117.P$6 (2)
unnamed: JP27.2, R117.P$8 (2)
unnamed: JP12.2, R32.P$6 (2)
unnamed: C184.1, U30.P$1 (TRACK/SS)
unnamed: R195.2, U30.P$2 (FREQ)
unnamed: C183.1, R194.1
unnamed: Q7.4G (G), U30.P$15 (BG)
unnamed: Q6.4G (G), U30.P$12 (TG)
unnamed: C170.1, D16.P$1 (C), U30.P$14 (BOOST)
unnamed: C201.1, R200.1, R201.2, U30.P$9 (VFB)
unnamed: R185.2, U30.P$6 (RUN)
unnamed: D15.2 (C), R184.1
unnamed: R16.1, R188.2, U30.P$3 (PLLIN/MODE)
unnamed: R186.2, U30.P$20 (ILIM)
unnamed: C166.1, R180.2, U30.P$17 (EXTVCC)
unnamed: JP12.3, R32.P$5 (2)
unnamed: JP24.2, R82.P$6 (2)
unnamed: JP24.3, R82.P$5 (2)
unnamed: JP34.2, R119.P$6 (2)
unnamed: JP34.3, R119.P$5 (2)
unnamed: JP27.3, R117.P$7 (2)
unnamed: R88.2, U15.P$8 (SCL)
unnamed: R86.2, U15.P$7 (SDA)
unnamed: R8.P$4 (1), U2.16 (SCLK)
unnamed: R8.P$2 (1), U2.14 (DIN)
unnamed: R8.P$1 (1), U2.1 (CS)
unnamed: R8.P$3 (1), U2.15 (DOUT)
unnamed: C10.1, R10.2
unnamed: C9.1, R9.2
unnamed: R204.1, U28.27 (BCBUS3)
unnamed: R187.1, U28.28 (BCBUS2)
OSC_IN: OSC.3@3 (OUT), U27.94 (IO_L40N_GCLK10_1)
PGOOD: R184.2, U30.P$18 (PGOOD)
PWR_DOWN: JP10.P$1, R34.2, R45.2, R56.2, R161.1, R167.1, R172.1, R185.1
REBOOT: JP41.P$2, R199.1, SW3.1, SW3.3 (P1), U27.37 (PROGRAM_B_2)
RESET: J2.5, R131.1, SW5.1, SW5.3 (P1), U19.13 (_RESET)
ROT1_A: R151.P$1 (1), U19.25 (PD4(D4/A6))
ROT1_B: R151.P$2 (1), U19.26 (PD6(D12/A7))
ROT2_A: R151.P$3 (1), U19.1 (PE6(D7)), U19.27 (PD7(D6*/A8))
ROT2_B: R151.P$4 (1), U19.28 (PB4(D8/A9))
ROUT_N: C47.1, C83.1, C118.1, U20.3 (COM1)
ROUT_P: C48.1, C101.1, C115.1, U20.9 (COM2)
RXD: U19.20 (PD2(INT2/RXD1/D0))
RXLED: D10.1 (A), U19.8 (PB0(SS){RXLED})
SCK: J2.3
SCL: R88.1, U19.18 (PD0(INT0/SCL/D3))
SCL_B: U10.14 (SCL)
SDA: R86.1, U19.19 (PD1(INT1/SDA/D2))
SDA_B: U10.13 (SDA)
SHUTDOWN: D8.CATHODE(2) (C), JP10.P$2, R56.1, R67.1, R94.1
TCK: JP39.4, R174.2, U27.109 (TCK)
TDI: JP39.2, R175.2, U27.110 (TDI)
TDO: JP39.3, U27.106 (TDO), U28.22 (ADBUS2)
TMS: JP39.1, R179.2, U27.107 (TMS)
TPA2008_EN: R65.2, R67.2, R76.2, U9.3 (_SHTDN)
TPA2008_VOL: JP20.2, R62.2, R68.2 (WIPER), R71.2, U9.14 (VOLUME)
TXD: U19.21 (PD3(INT3/TXD1/D1))
TXLED: D11.1 (A), U19.22 (PD5(TXLED))
USBDM_A: R181.2, U28.8 (USBDM)
USBDP_A: R182.2, R183.1, U28.7 (USBDP)
USB_ID: JP30.ID
USB_RXD: U27.105 (IO_L1P_1), U28.39 (BDBUS1)
USB_TCK: R174.1, U28.24 (ADBUS0)
USB_TDI: R175.1, U28.23 (ADBUS1)
USB_TMS: R179.1, U28.21 (ADBUS3)
USB_TXD: U27.101 (IO_L32N_1), U28.40 (BDBUS0)
VBATT: C19.P$2 (+), C20.P$1 (1), C21.1, JP1.2, Q4.2/HEAT (D), R18.P$1 (1), R46.2, R47.2, R49.1, U3.P$6 (BATT)
VBUS: C109.1, C143.1, D4.P$2 (A), JP30.VBUS, JP40.VBUS, U13.5 (VBUS), U19.2 (UVCC), U19.7 (VBUS)
VCCIO: C74.1, C75.1, IC1.2/HEAT (3_OUT), L1.1, R1.2, R2.2, R3.P$5 (2), R3.P$6 (2), R3.P$7 (2), R3.P$8 (2), R21.2, R22.2, R37.2, R53.2, R93.2, R114.2, R143.2, R144.2, U5.8 (V+), U11.8 (V+), U14.8 (V+), U15.P$12 (VDD), U15.P$20 (VDD), U17.8 (V+), U18.1 (VCC), U20.1 (VCC)
VDD: C136.1, R158.2, U24.5 (OUT)
VIN: C130.P$1 (1), C131.1, C172.P$1 (1), C173.P$1 (1), C174.P$1 (1), C175.P$1 (1), C176.P$1 (1), C177.P$1 (1), C178.P$1 (1), C179.P$2 (+), C180.P$2 (+), C181.P$2 (+), D15.1 (A), Q3.2/HEAT (D), Q5.2/HEAT (D), Q6.PAD (D), Q6.PAD2 (D), R29.2, R34.1, R39.2, R157.2, U7.P$17 (VS), U23.P$4 (VIN), U30.P$19 (VIN)
VM: R46.1, R54.2, U7.P$4 (VM)
VWALL: C11.1, C12.P$1 (1), D1.P$2 (A), D4.P$1 (C), J1.PWR, JP2.2, Q1.7 (D), Q1.8 (D), Q2.2/HEAT (D), R11.2, R12.2, R41.2, R48.2, R51.1
W1_A1: R122.P$6 (2), U16.8 (A7), U27.48 (IO_L48P_D7_2)
W1_A2: R122.P$8 (2), U16.6 (A5), U27.51 (IO_L31P_GCLK31_D14_2)
W1_A3: R121.P$6 (2), U16.4 (A3), U27.56 (IO_L30P_GCLK1_D13_2)
W1_A4: R121.P$8 (2), U16.2 (A1), U27.58 (IO_L14P_D11_2)
W1_A5: R43.P$6 (2), U6.8 (A7), U27.61 (IO_L12N_D2_MISO3_2)
W1_A6: R43.P$8 (2), U6.6 (A5), U27.66 (IO_L2N_CMPMOSI_2)
W1_A7: R42.P$5 (2), U6.5 (A4), U27.67 (IO_L2P_CMPCLK_2)
W1_A8: R42.P$7 (2), U6.3 (A2), U27.75 (IO_L74P_AWAKE_1)
W1_A9: R73.P$5 (2), U8.9 (A8), U27.79 (IO_L47P_1)
W1_A10: R73.P$6 (2), U8.8 (A7), U27.81 (IO_L46P_1)
W1_A11: R73.P$8 (2), U8.6 (A5), U27.83 (IO_L45P_1)
W1_A12: R72.P$6 (2), U8.4 (A3), U27.85 (IO_L43P_GCLK5_1)
W1_A13: R72.P$8 (2), U8.2 (A1), U27.88 (IO_L42P_GCLK7_1)
W1_A14: U27.93 (IO_L41P_GCLK9_IRDY1_1)
W1_A15: U27.98 (IO_L34P_1)
W1_A16: U27.100 (IO_L33P_1)
W1_B1: U27.99 (IO_L33N_1)
W1_B2: U27.97 (IO_L34N_1)
W1_B3: U27.92 (IO_L41N_GCLK8_1)
W1_B4: R72.P$7 (2), U8.3 (A2), U27.87 (IO_L42N_GCLK6_TRDY1_1)
W1_B5: R72.P$5 (2), U8.5 (A4), U27.84 (IO_L43N_GCLK4_1)
W1_B6: R73.P$7 (2), U8.7 (A6), U27.82 (IO_L45N_1)
W1_B7: U27.80 (IO_L46N_1)
W1_B8: R42.P$8 (2), U6.2 (A1), U27.78 (IO_L47N_1)
W1_B9: R42.P$6 (2), U6.4 (A3), U27.74 (IO_L74N_DOUT_BUSY_1)
W1_B10: U27.95 (IO_L40P_GCLK11_1)
W1_B11: R43.P$7 (2), U6.7 (A6), U27.62 (IO_L12P_D1_MISO2_2)
W1_B12: R43.P$5 (2), U6.9 (A8), U27.59 (IO_L13N_D10_2)
W1_B13: R121.P$7 (2), U16.3 (A2), U27.57 (IO_L14N_D12_2)
W1_B14: R121.P$5 (2), U16.5 (A4), U27.55 (IO_L30N_GCLK0_USERCCLK_2)
W1_B15: R122.P$7 (2), U16.7 (A6), U27.50 (IO_L31N_GCLK30_D15_2)
W1_B16: R122.P$5 (2), U16.9 (A8), U27.47 (IO_L48N_RDWR_B_VREF_2)
W2_A1: U27.114 (IO_L65N_SCP2_0)
W2_A2: U27.115 (IO_L65P_SCP3_0)
W2_A3: U27.116 (IO_L64N_SCP4_0)
W2_A4: U27.117 (IO_L64P_SCP5_0)
W2_A5: U27.118 (IO_L63N_SCP6_0)
W2_A6: U27.119 (IO_L63P_SCP7_0)
W2_A7: U27.120 (IO_L62N_VREF_0)
W2_A8: U27.121 (IO_L62P_0)
W2_A9: U27.123 (IO_L37N_GCLK12_0)
W2_A10: U27.124 (IO_L37P_GCLK13_0)
W2_A11: U27.126 (IO_L36N_GCLK14_0)
W2_A12: U27.127 (IO_L36P_GCLK15_0)
W2_A13: U27.131 (IO_L35N_GCLK16_0)
W2_A14: U27.132 (IO_L35P_GCLK17_0)
W2_A15: U27.133 (IO_L34N_GCLK18_0)
W2_A16: U27.134 (IO_L34P_GCLK19_0)
WDE: JP9.2, U7.P$6 (WDE)
XTIN_A: C165.2, U28.43 (XTIN), X2.3 (3A)
XTOUT_A: C168.2, U28.44 (XTOUT), X2.1 (1A)
_KILL: JP9.3, U7.P$3 (_KILL)

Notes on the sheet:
Rotary Encoder connector
Bluetooth
Atmega32u4 Microcontroller
SPI ADC
Confirm the Sync pin
MIDI Input
93LC46B
LED Strip Circuits
SPI Flash
JTAG Configuration
HSWAP low pulls up all pins during configuration
M0 high, M1 low puts FPGA in Master Serial / SPI mode
PROG_B asserted causes a JTAG reconfiguration
Power Requirements
VCCINT requires 1.2V
VCCAUX requires 3.3V
VCCO's are 3.3V (no longer selectable)
JTAG
Copyright 2012 Gadget Factory, LLC
See more details at www.GadgetFactory.net
This work is licensed under the Creative Commons Attribution-NonCommercial-ShareAlike License.
To view a copy of this license, visit http://creativecommons.org/ ; or, (b) send a letter to Creative Commons, 171 2nd Street, Suite 300, San Francisco, California, 94105, USA.
Power Section
USB Section
FPGA Section
REBOOT
Review these pins
Power input and battery charger
Alternative 3.3V LDO
Power regulators (5V, 3.3V, 1.2V)
Audio
Speaker driver and aux out
Differential audio routing
Bluetooth and microphone
Dynamic and electret micophone input
Power input and battery
Atmega32u4 and inputs
Papilio Pro
Accelerometer
Buffer transcievers
